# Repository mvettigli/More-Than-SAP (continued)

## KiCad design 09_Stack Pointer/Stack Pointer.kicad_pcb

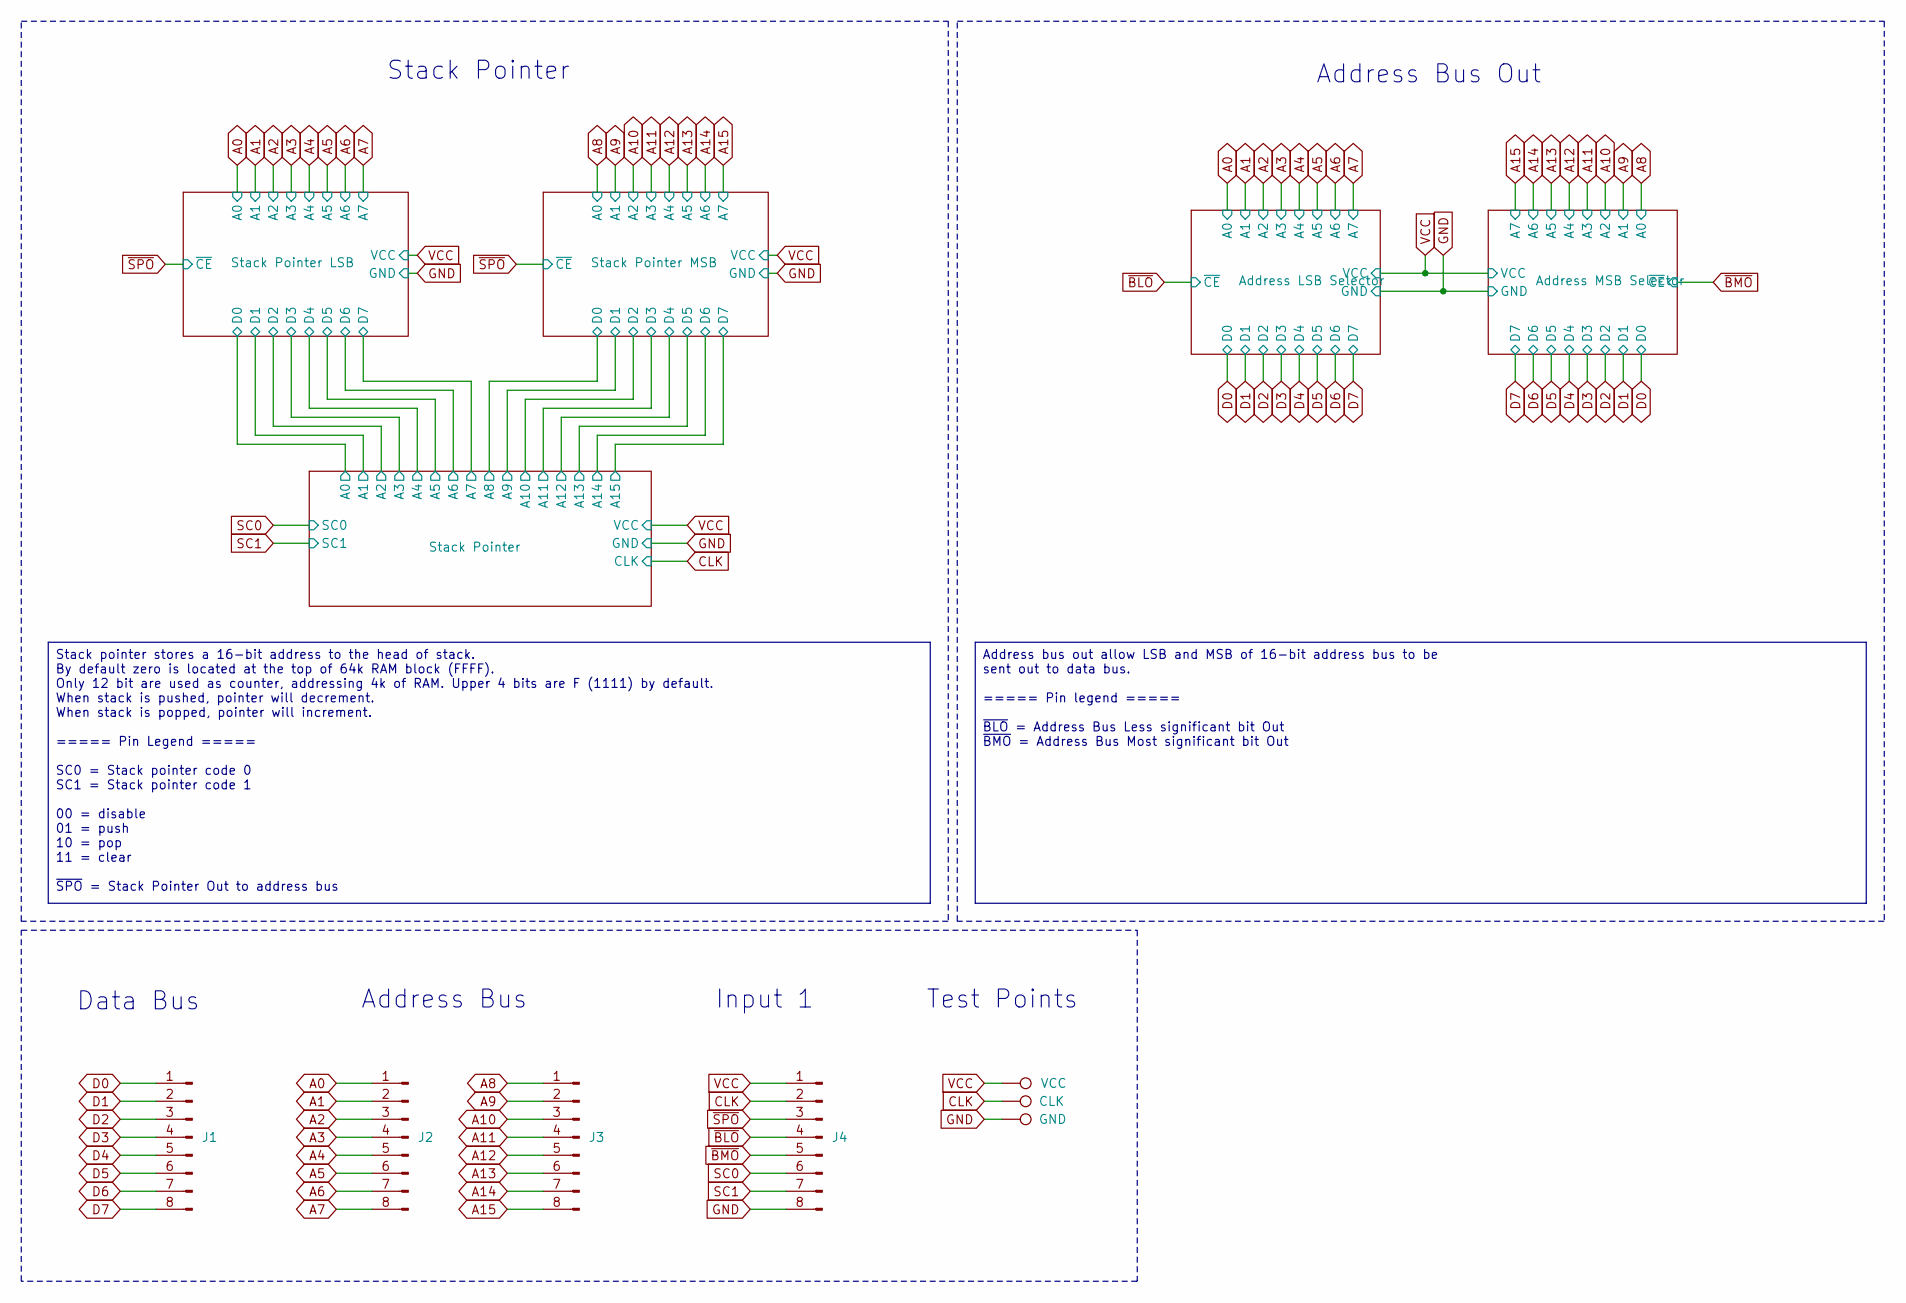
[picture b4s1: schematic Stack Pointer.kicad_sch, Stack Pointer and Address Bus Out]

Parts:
J1: Data bus; PinHeader_1x08_P2.54mm_Horizontal
J2: Address bus 1; PinHeader_1x08_P2.54mm_Horizontal
J3: Address bus 2; PinHeader_1x08_P2.54mm_Horizontal
J4: Input 1; PinHeader_1x08_P2.54mm_Horizontal
TP1: VCC; TestPoint_Loop_D3.50mm_Drill0.9mm_Beaded
TP2: CLK; TestPoint_Loop_D3.50mm_Drill0.9mm_Beaded
TP3: GND; TestPoint_Loop_D3.50mm_Drill0.9mm_Beaded

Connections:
A0: J2.1; also elsewhere on the board
A1: J2.2; also elsewhere on the board
A2: J2.3; also elsewhere on the board
A3: J2.4; also elsewhere on the board
A4: J2.5; also elsewhere on the board
A5: J2.6; also elsewhere on the board
A6: J2.7; also elsewhere on the board
A7: J2.8; also elsewhere on the board
A8: J3.1; also elsewhere on the board
A9: J3.2; also elsewhere on the board
A10: J3.3; also elsewhere on the board
A11: J3.4; also elsewhere on the board
A12: J3.5; also elsewhere on the board
A13: J3.6; also elsewhere on the board
A14: J3.7; also elsewhere on the board
A15: J3.8; also elsewhere on the board
CLK: J4.2, TP2.1; also elsewhere on the board
D0: J1.1; also elsewhere on the board
D1: J1.2; also elsewhere on the board
D2: J1.3; also elsewhere on the board
D3: J1.4; also elsewhere on the board
D4: J1.5; also elsewhere on the board
D5: J1.6; also elsewhere on the board
D6: J1.7; also elsewhere on the board
D7: J1.8; also elsewhere on the board
GND: J4.8, TP3.1; also elsewhere on the board
SC0: J4.6; also elsewhere on the board
SC1: J4.7; also elsewhere on the board
VCC: J4.1, TP1.1; also elsewhere on the board
~BLO: J4.4; also elsewhere on the board
~BMO: J4.5; also elsewhere on the board
~SPO: J4.3; also elsewhere on the board

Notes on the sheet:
Stack Pointer
Address Bus Out
Address Bus
Data Bus
Test Points
Input 1
Address bus out allow LSB and MSB of 16-bit address bus to be sent out to data bus. ===== Pin legend ===== ~{BLO} = Address Bus Less significant bit Out ~{BMO} = Address Bus Most significant bit Out
Stack pointer stores a 16-bit address to the head of stack. By default zero is located at the top of 64k RAM block (FFFF). Only 12 bit are used as counter, addressing 4k of RAM. Upper 4 bits are F (1111) by default. When stack is pushed, pointer will decrement. When stack is popped, pointer will in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

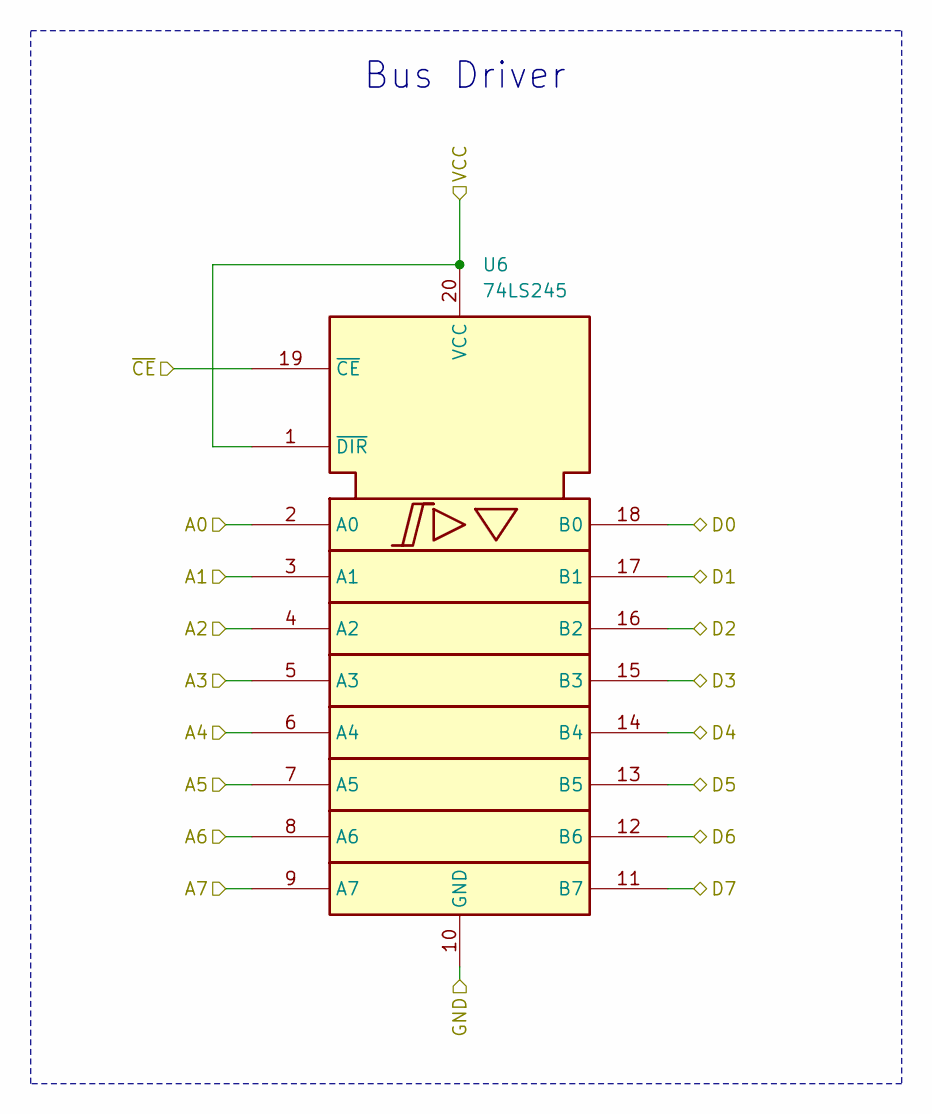
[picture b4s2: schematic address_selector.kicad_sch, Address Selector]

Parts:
U6: 74LS245; DIP-20_W7.62mm

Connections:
/Stack Pointer/A0: U6.18 (B0); also elsewhere on the board
/Stack Pointer/A1: U6.17 (B1); also elsewhere on the board
/Stack Pointer/A2: U6.16 (B2); also elsewhere on the board
/Stack Pointer/A3: U6.15 (B3); also elsewhere on the board
/Stack Pointer/A4: U6.14 (B4); also elsewhere on the board
/Stack Pointer/A5: U6.13 (B5); also elsewhere on the board
/Stack Pointer/A6: U6.12 (B6); also elsewhere on the board
/Stack Pointer/A7: U6.11 (B7); also elsewhere on the board
A0: U6.2 (A0); also elsewhere on the board
A1: U6.3 (A1); also elsewhere on the board
A2: U6.4 (A2); also elsewhere on the board
A3: U6.5 (A3); also elsewhere on the board
A4: U6.6 (A4); also elsewhere on the board
A5: U6.7 (A5); also elsewhere on the board
A6: U6.8 (A6); also elsewhere on the board
A7: U6.9 (A7); also elsewhere on the board
GND: U6.10 (GND); also elsewhere on the board
VCC: U6.1 (~DIR), U6.20 (VCC); also elsewhere on the board
~SPO: U6.19 (~CE); also elsewhere on the board

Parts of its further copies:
U7, U8, U9: 74LS245; DIP-20_W7.62mm

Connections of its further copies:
/Stack Pointer MSB/D0: U7.18 (B0); also elsewhere on the board
/Stack Pointer MSB/D1: U7.17 (B1); also elsewhere on the board
/Stack Pointer MSB/D2: U7.16 (B2); also elsewhere on the board
/Stack Pointer MSB/D3: U7.15 (B3); also elsewhere on the board
A0: U8.2 (A0); also elsewhere on the board
A1: U8.3 (A1); also elsewhere on the board
A2: U8.4 (A2); also elsewhere on the board
A3: U8.5 (A3); also elsewhere on the board
A4: U8.6 (A4); also elsewhere on the board
A5: U8.7 (A5); also elsewhere on the board
A6: U8.8 (A6); also elsewhere on the board
A7: U8.9 (A7); also elsewhere on the board
A8: U7.2 (A0), U9.2 (A0); also elsewhere on the board
A9: U7.3 (A1), U9.3 (A1); also elsewhere on the board
A10: U7.4 (A2), U9.4 (A2); also elsewhere on the board
A11: U7.5 (A3), U9.5 (A3); also elsewhere on the board
A12: U7.6 (A4), U9.6 (A4); also elsewhere on the board
A13: U7.7 (A5), U9.7 (A5); also elsewhere on the board
A14: U7.8 (A6), U9.8 (A6); also elsewhere on the board
A15: U7.9 (A7), U9.9 (A7); also elsewhere on the board
D0: U8.18 (B0), U9.18 (B0); also elsewhere on the board
D1: U8.17 (B1), U9.17 (B1); also elsewhere on the board
D2: U8.16 (B2), U9.16 (B2); also elsewhere on the board
D3: U8.15 (B3), U9.15 (B3); also elsewhere on the board
D4: U8.14 (B4), U9.14 (B4); also elsewhere on the board
D5: U8.13 (B5), U9.13 (B5); also elsewhere on the board
D6: U8.12 (B6), U9.12 (B6); also elsewhere on the board
D7: U8.11 (B7), U9.11 (B7); also elsewhere on the board
GND: U7.10 (GND), U8.10 (GND), U9.10 (GND); also elsewhere on the board
VCC: U7.1 (~DIR), U7.11 (B7), U7.12 (B6), U7.13 (B5), U7.14 (B4), U7.20 (VCC), U8.1 (~DIR), U8.20 (VCC), U9.1 (~DIR), U9.20 (VCC); also elsewhere on the board
~BLO: U8.19 (~CE); also elsewhere on the board
~BMO: U9.19 (~CE); also elsewhere on the board
~SPO: U7.19 (~CE); also elsewhere on the board

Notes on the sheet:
Bus Driver

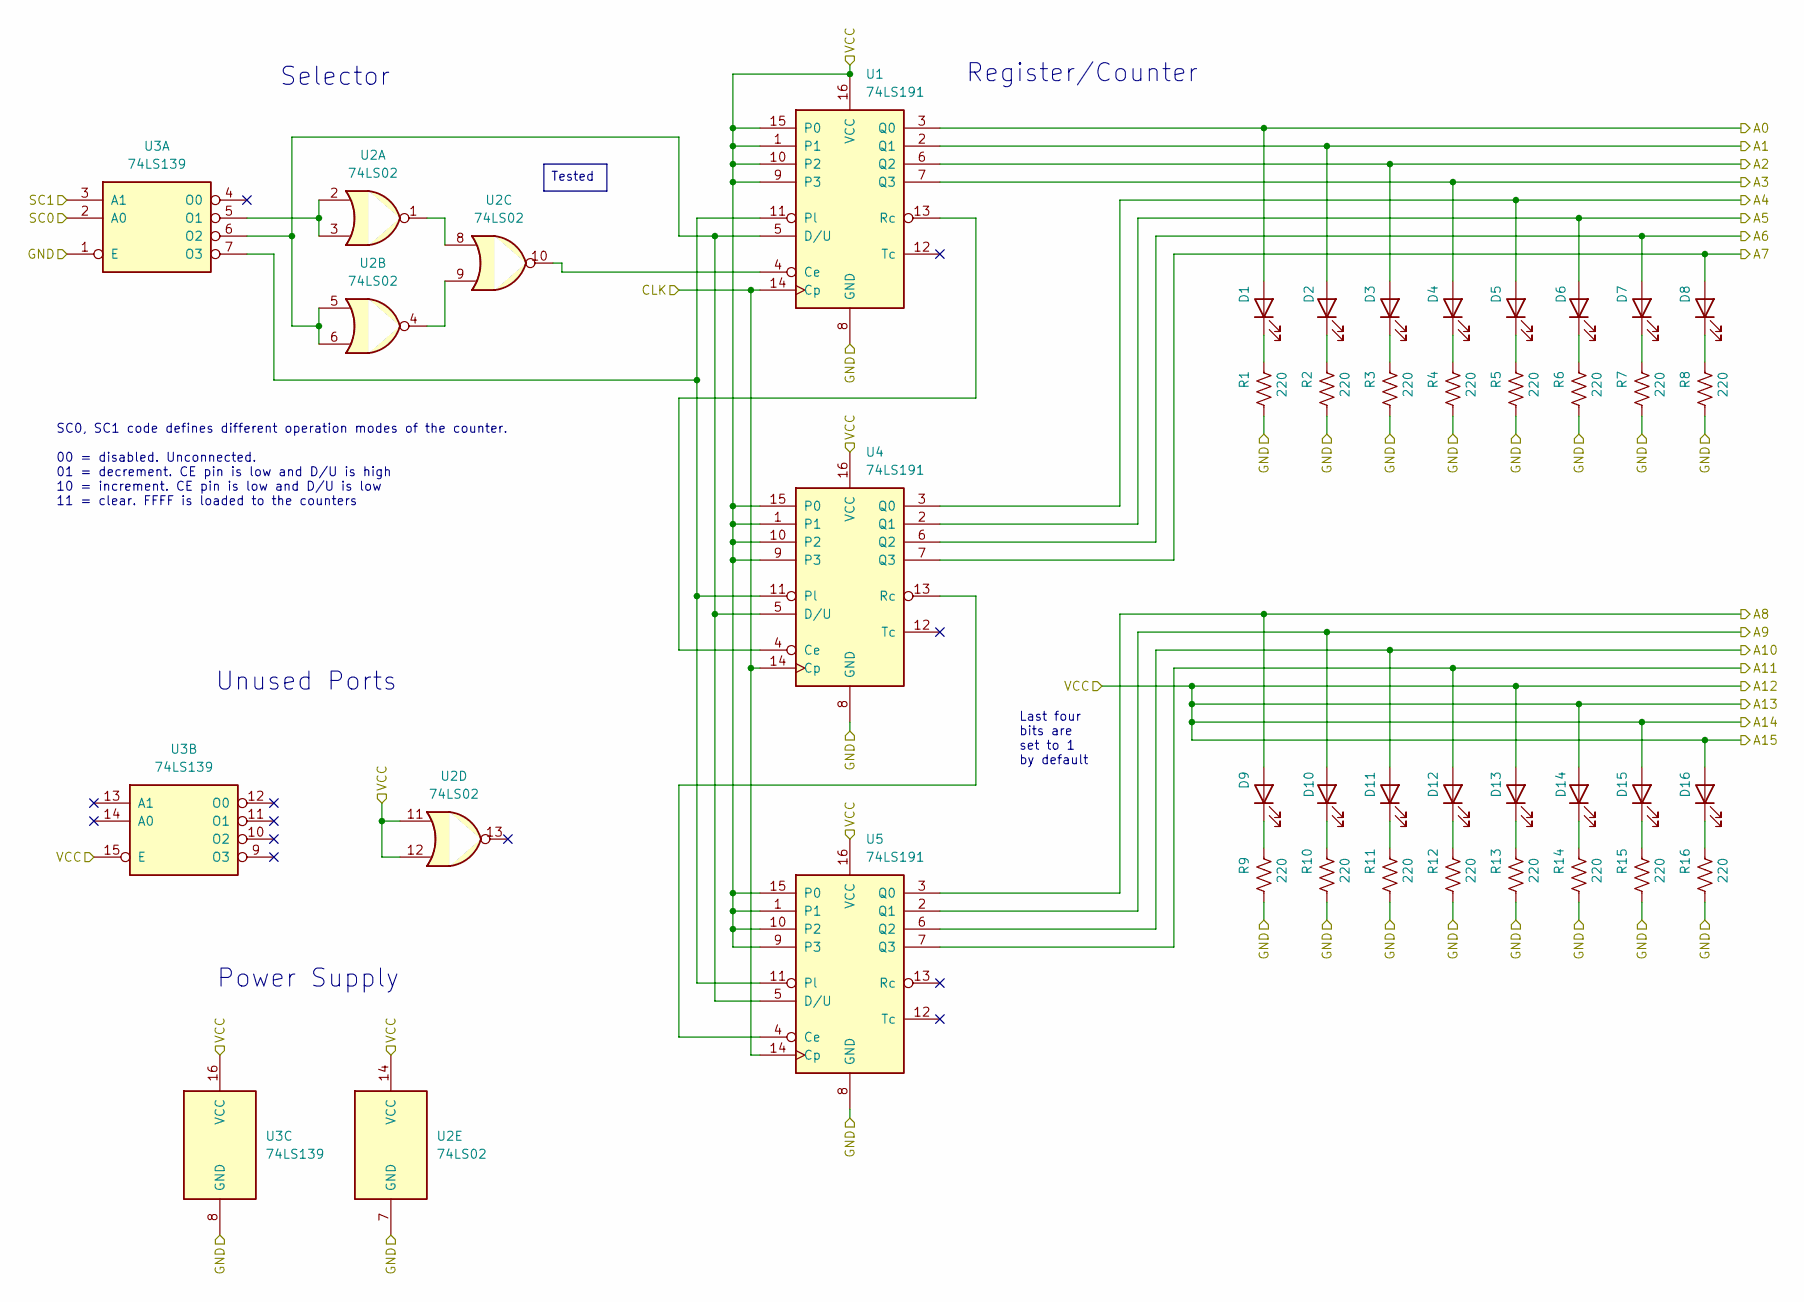
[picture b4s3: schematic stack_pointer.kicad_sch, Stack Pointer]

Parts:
D1, D2, D3, D4, D5, D6, D7, D8, D9, D10, D11, D12, D13, D14, D15, D16: GREEN; LED_D3.0mm
R1, R2, R3, R4, R5, R6, R7, R8, R9, R10, R11, R12, R13, R14, R15, R16: 220; R_Axial_DIN0207_L6.3mm_D2.5mm_P10.16mm_Horizontal
U1, U4, U5: 74LS191; DIP-16_W7.62mm
U2: 74LS02; DIP-14_W7.62mm
U3: 74LS139; DIP-16_W7.62mm

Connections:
/Stack Pointer MSB/D0: D9.2 (A), U5.3 (Q0); also elsewhere on the board
/Stack Pointer MSB/D1: D10.2 (A), U5.2 (Q1); also elsewhere on the board
/Stack Pointer MSB/D2: D11.2 (A), U5.6 (Q2); also elsewhere on the board
/Stack Pointer MSB/D3: D12.2 (A), U5.7 (Q3); also elsewhere on the board
/Stack Pointer/A0: D1.2 (A), U1.3 (Q0); also elsewhere on the board
/Stack Pointer/A1: D2.2 (A), U1.2 (Q1); also elsewhere on the board
/Stack Pointer/A2: D3.2 (A), U1.6 (Q2); also elsewhere on the board
/Stack Pointer/A3: D4.2 (A), U1.7 (Q3); also elsewhere on the board
/Stack Pointer/A4: D5.2 (A), U4.3 (Q0); also elsewhere on the board
/Stack Pointer/A5: D6.2 (A), U4.2 (Q1); also elsewhere on the board
/Stack Pointer/A6: D7.2 (A), U4.6 (Q2); also elsewhere on the board
/Stack Pointer/A7: D8.2 (A), U4.7 (Q3); also elsewhere on the board
CLK: U1.14 (Cp), U4.14 (Cp), U5.14 (Cp); also elsewhere on the board
GND: R1.2, R2.2, R3.2, R4.2, R5.2, R6.2, R7.2, R8.2, R9.2, R10.2, R11.2, R12.2, R13.2, R14.2, R15.2, R16.2, U1.8 (GND), U2.7 (GND), U3.1 (E), U3.8 (GND), U4.8 (GND), U5.8 (GND); also elsewhere on the board
unnamed: D1.1 (K), R1.1
unnamed: D2.1 (K), R2.1
unnamed: D3.1 (K), R3.1
unnamed: D4.1 (K), R4.1
unnamed: D5.1 (K), R5.1
unnamed: D6.1 (K), R6.1
unnamed: D7.1 (K), R7.1
unnamed: D8.1 (K), R8.1
unnamed: D9.1 (K), R9.1
unnamed: D10.1 (K), R10.1
unnamed: D11.1 (K), R11.1
unnamed: D12.1 (K), R12.1
unnamed: D13.1 (K), R13.1
unnamed: D14.1 (K), R14.1
unnamed: D15.1 (K), R15.1
unnamed: D16.1 (K), R16.1
unnamed: U1.4 (Ce), U2.10
unnamed: U1.5 (D/U), U2.5, U2.6, U3.6 (O2), U4.5 (D/U), U5.5 (D/U)
unnamed: U1.11 (Pl), U3.7 (O3), U4.11 (Pl), U5.11 (Pl)
unnamed: U1.13 (Rc), U4.4 (Ce)
unnamed: U2.1, U2.8
unnamed: U2.4, U2.9
unnamed: U2.2, U2.3, U3.5 (O1)
unnamed: U4.13 (Rc), U5.4 (Ce)
SC0: U3.2 (A0); also elsewhere on the board
SC1: U3.3 (A1); also elsewhere on the board
VCC: D13.2 (A), D14.2 (A), D15.2 (A), D16.2 (A), U1.1, U1.9 (P3), U1.10 (P2), U1.15 (P0), U1.16 (VCC), U2.11, U2.12, U2.14 (VCC), U3.15 (E), U3.16 (VCC), U4.1, U4.9 (P3), U4.10 (P2), U4.15 (P0), U4.16 (VCC), U5.1, U5.9 (P3), U5.10 (P2), U5.15 (P0), U5.16 (VCC); also elsewhere on the board

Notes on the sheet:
Selector
Unused Ports
Power Supply
Register/Counter
SC0, SC1 code defines different operation modes of the counter. 00 = disabled. Unconnected. 01 = decrement. CE pin is low and D/U is high 10 = increment. CE pin is low and D/U is low 11 = clear. FFFF is loaded to the counters
Last four bits are set to 1 by default
Tested

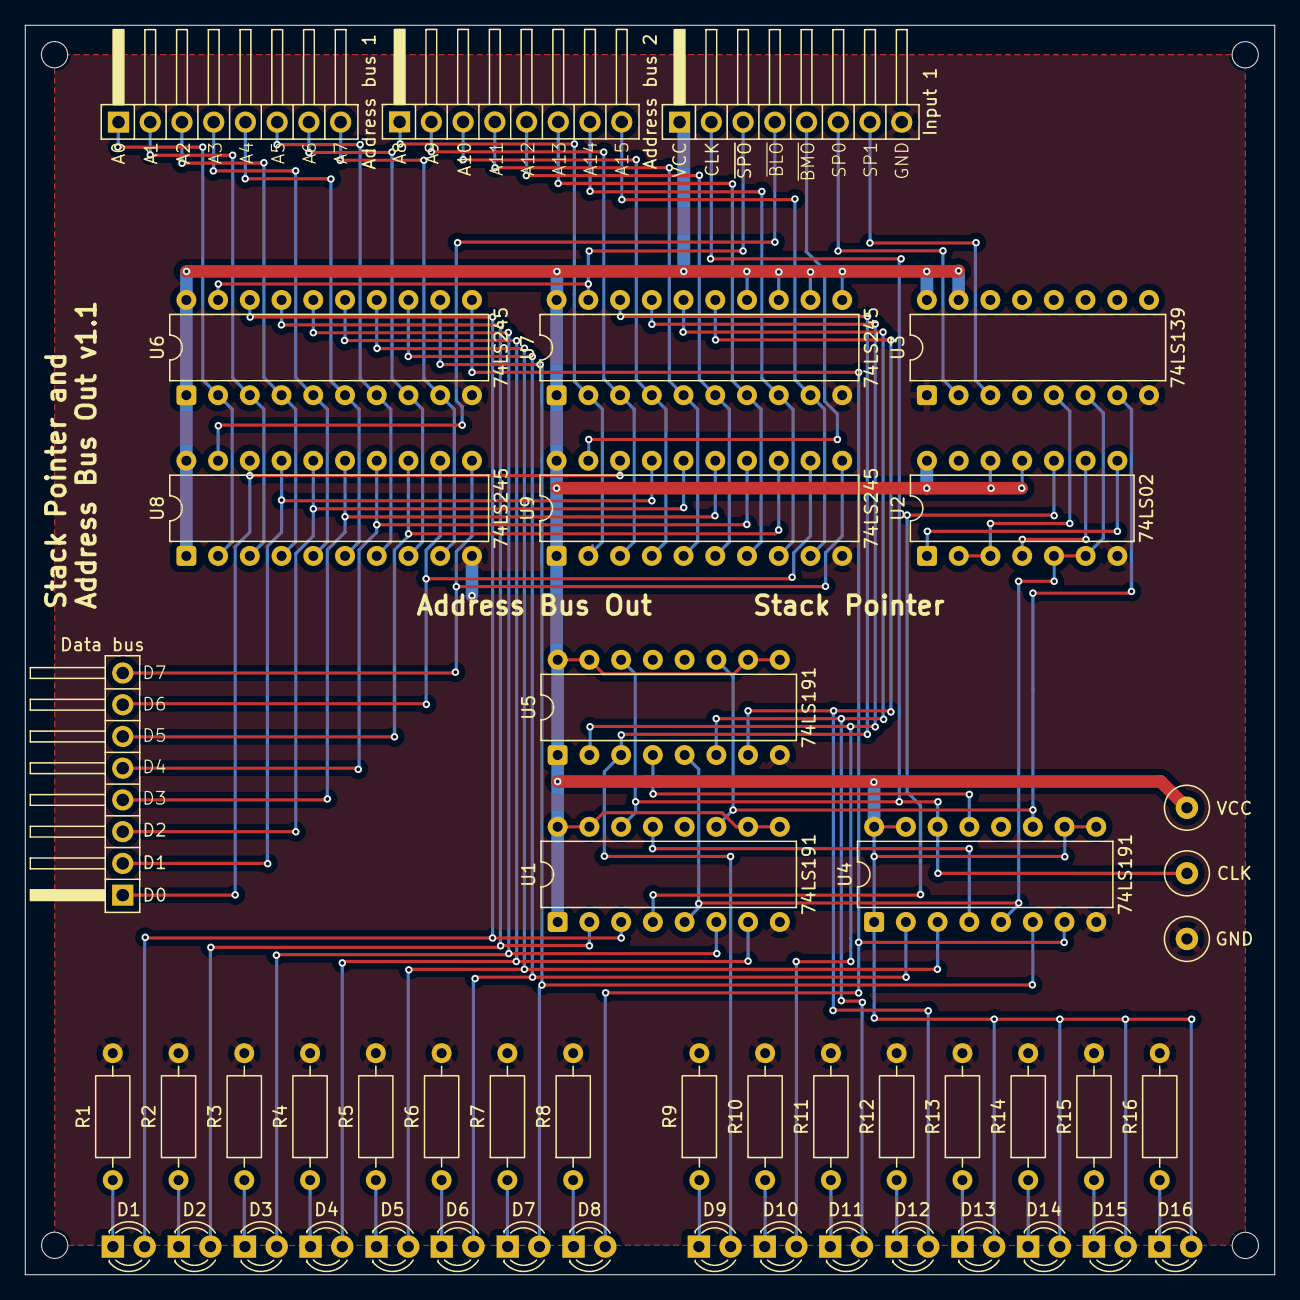
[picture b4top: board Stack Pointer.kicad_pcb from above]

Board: 2 copper layers, 100.0 x 100.0 mm, 48 parts (0 on the bottom side), 68 nets.

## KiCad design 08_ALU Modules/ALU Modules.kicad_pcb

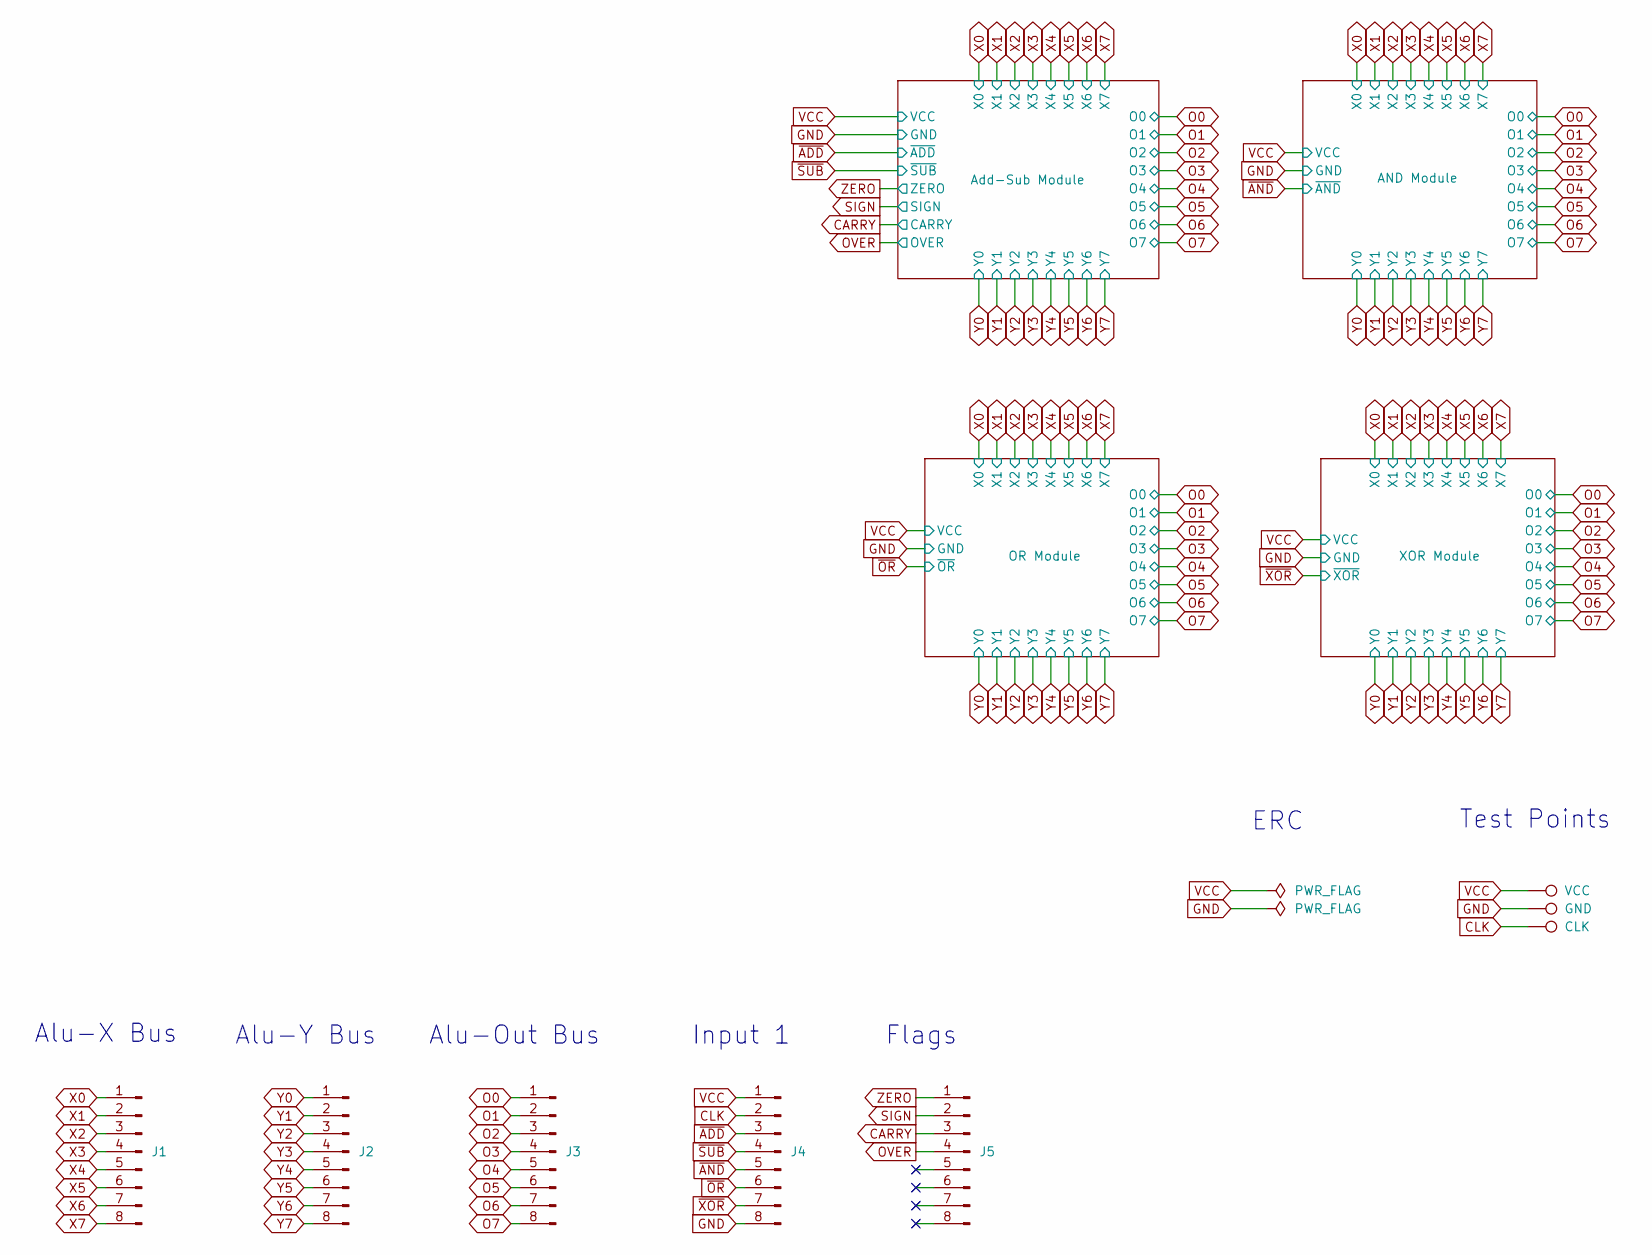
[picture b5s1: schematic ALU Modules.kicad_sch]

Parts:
J1: Alu-X Bus; PinHeader_1x08_P2.54mm_Horizontal
J2: Alu-Y Bus; PinHeader_1x08_P2.54mm_Horizontal
J3: Alu-Out Bus; PinHeader_1x08_P2.54mm_Horizontal
J4: Input 1; PinHeader_1x08_P2.54mm_Horizontal
J5: Flags; PinHeader_1x08_P2.54mm_Horizontal
TP1: VCC; TestPoint_Loop_D3.50mm_Drill0.9mm_Beaded
TP2: GND; TestPoint_Loop_D3.50mm_Drill0.9mm_Beaded
TP3: CLK; TestPoint_Loop_D3.50mm_Drill0.9mm_Beaded

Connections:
CARRY: J5.3; also elsewhere on the board
CLK: J4.2, TP3.1
GND: J4.8, TP2.1; also elsewhere on the board
O0: J3.1; also elsewhere on the board
O1: J3.2; also elsewhere on the board
O2: J3.3; also elsewhere on the board
O3: J3.4; also elsewhere on the board
O4: J3.5; also elsewhere on the board
O5: J3.6; also elsewhere on the board
O6: J3.7; also elsewhere on the board
O7: J3.8; also elsewhere on the board
OVER: J5.4; also elsewhere on the board
SIGN: J5.2; also elsewhere on the board
VCC: J4.1, TP1.1; also elsewhere on the board
X0: J1.1; also elsewhere on the board
X1: J1.2; also elsewhere on the board
X2: J1.3; also elsewhere on the board
X3: J1.4; also elsewhere on the board
X4: J1.5; also elsewhere on the board
X5: J1.6; also elsewhere on the board
X6: J1.7; also elsewhere on the board
X7: J1.8; also elsewhere on the board
Y0: J2.1; also elsewhere on the board
Y1: J2.2; also elsewhere on the board
Y2: J2.3; also elsewhere on the board
Y3: J2.4; also elsewhere on the board
Y4: J2.5; also elsewhere on the board
Y5: J2.6; also elsewhere on the board
Y6: J2.7; also elsewhere on the board
Y7: J2.8; also elsewhere on the board
ZERO: J5.1; also elsewhere on the board
~ADD: J4.3; also elsewhere on the board
~AND: J4.5; also elsewhere on the board
~OR: J4.6; also elsewhere on the board
~SUB: J4.4; also elsewhere on the board
~XOR: J4.7; also elsewhere on the board

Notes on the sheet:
Test Points
Flags
Alu-X Bus
Alu-Y Bus
Alu-Out Bus
Input 1
ERC

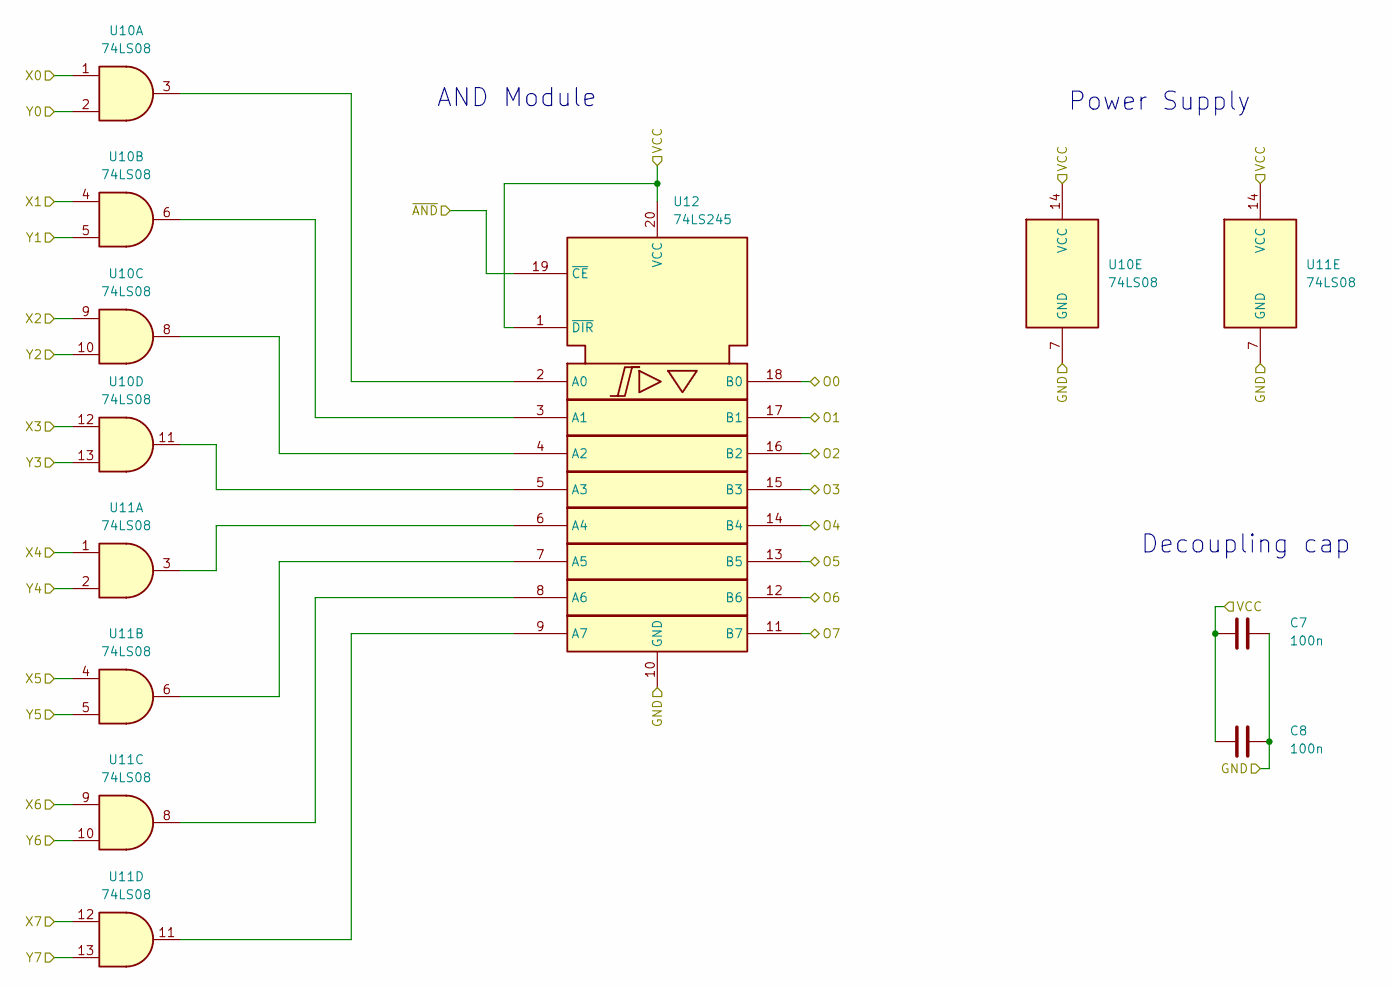
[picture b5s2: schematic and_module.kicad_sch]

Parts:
C7, C8: 100n; C_Disc_D3.0mm_W1.6mm_P2.50mm
U10, U11: 74LS08; DIP-14_W7.62mm
U12: 74LS245; DIP-20_W7.62mm

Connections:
GND: C7.2, C8.2, U10.7 (GND), U11.7 (GND), U12.10 (GND); also elsewhere on the board
unnamed: U10.3, U12.2 (A0)
unnamed: U10.6, U12.3 (A1)
unnamed: U10.8, U12.4 (A2)
unnamed: U10.11, U12.5 (A3)
unnamed: U11.3, U12.6 (A4)
unnamed: U11.6, U12.7 (A5)
unnamed: U11.8, U12.8 (A6)
unnamed: U11.11, U12.9 (A7)
O0: U12.18 (B0); also elsewhere on the board
O1: U12.17 (B1); also elsewhere on the board
O2: U12.16 (B2); also elsewhere on the board
O3: U12.15 (B3); also elsewhere on the board
O4: U12.14 (B4); also elsewhere on the board
O5: U12.13 (B5); also elsewhere on the board
O6: U12.12 (B6); also elsewhere on the board
O7: U12.11 (B7); also elsewhere on the board
VCC: C7.1, C8.1, U10.14 (VCC), U11.14 (VCC), U12.1 (~DIR), U12.20 (VCC); also elsewhere on the board
X0: U10.1; also elsewhere on the board
X1: U10.4; also elsewhere on the board
X2: U10.9; also elsewhere on the board
X3: U10.12; also elsewhere on the board
X4: U11.1; also elsewhere on the board
X5: U11.4; also elsewhere on the board
X6: U11.9; also elsewhere on the board
X7: U11.12; also elsewhere on the board
Y0: U10.2; also elsewhere on the board
Y1: U10.5; also elsewhere on the board
Y2: U10.10; also elsewhere on the board
Y3: U10.13; also elsewhere on the board
Y4: U11.2; also elsewhere on the board
Y5: U11.5; also elsewhere on the board
Y6: U11.10; also elsewhere on the board
Y7: U11.13; also elsewhere on the board
~AND: U12.19 (~CE); also elsewhere on the board

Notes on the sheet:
AND Module
Power Supply
Decoupling cap

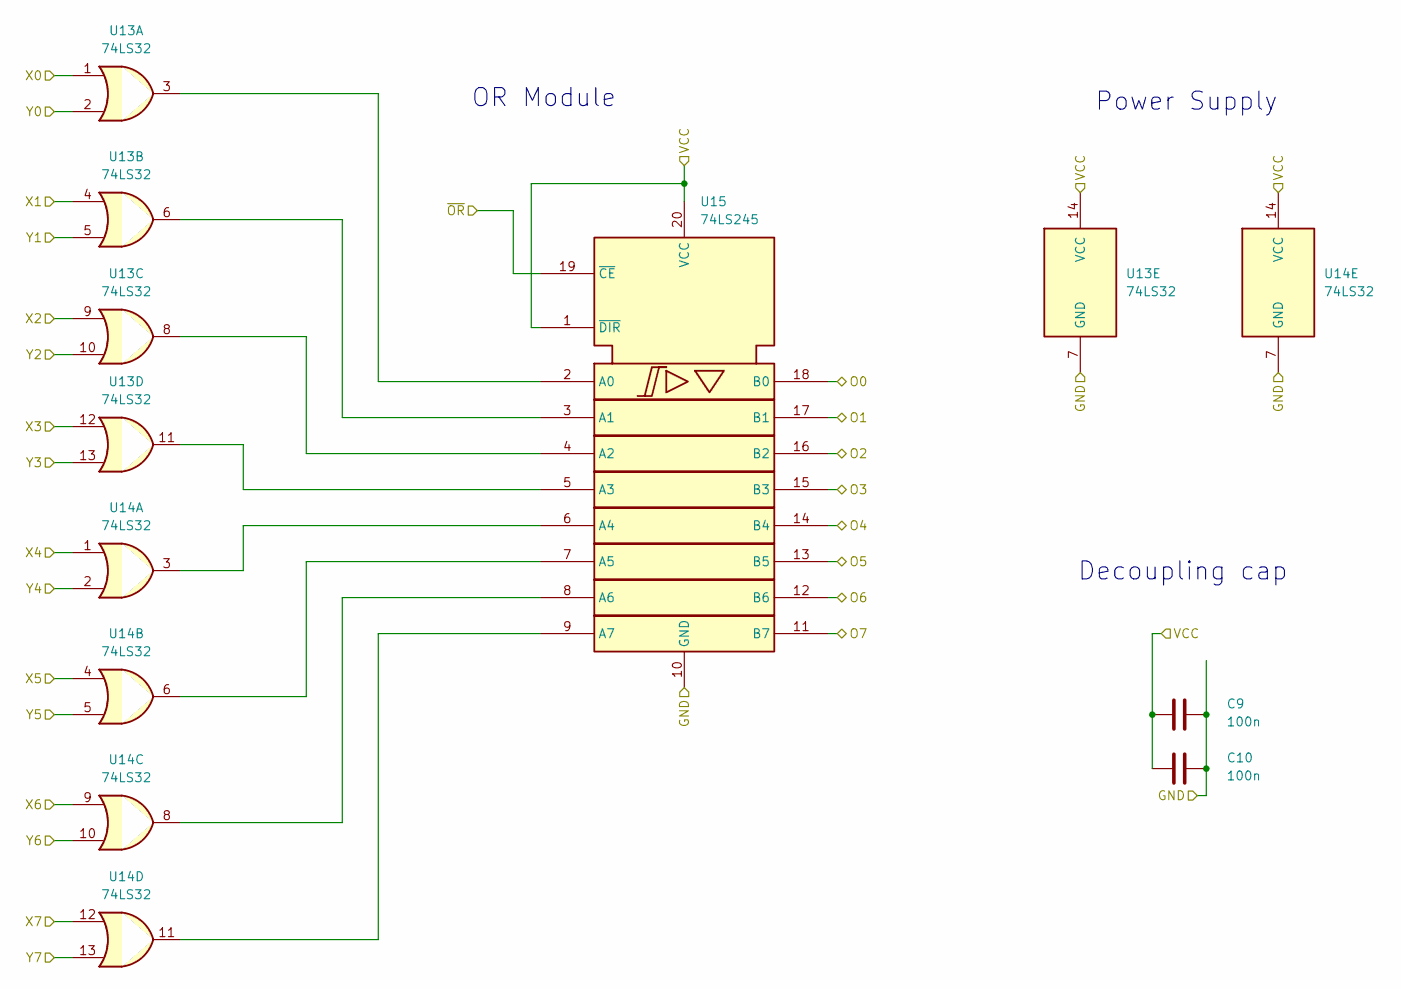
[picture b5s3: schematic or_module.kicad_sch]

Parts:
C9, C10: 100n; C_Disc_D3.0mm_W1.6mm_P2.50mm
U13, U14: 74LS32; DIP-14_W7.62mm
U15: 74LS245; DIP-20_W7.62mm

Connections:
GND: C9.2, C10.2, U13.7 (GND), U14.7 (GND), U15.10 (GND); also elsewhere on the board
unnamed: U13.3, U15.2 (A0)
unnamed: U13.6, U15.3 (A1)
unnamed: U13.8, U15.4 (A2)
unnamed: U13.11, U15.5 (A3)
unnamed: U14.3, U15.6 (A4)
unnamed: U14.6, U15.7 (A5)
unnamed: U14.8, U15.8 (A6)
unnamed: U14.11, U15.9 (A7)
O0: U15.18 (B0); also elsewhere on the board
O1: U15.17 (B1); also elsewhere on the board
O2: U15.16 (B2); also elsewhere on the board
O3: U15.15 (B3); also elsewhere on the board
O4: U15.14 (B4); also elsewhere on the board
O5: U15.13 (B5); also elsewhere on the board
O6: U15.12 (B6); also elsewhere on the board
O7: U15.11 (B7); also elsewhere on the board
VCC: C9.1, C10.1, U13.14 (VCC), U14.14 (VCC), U15.1 (~DIR), U15.20 (VCC); also elsewhere on the board
X0: U13.1; also elsewhere on the board
X1: U13.4; also elsewhere on the board
X2: U13.9; also elsewhere on the board
X3: U13.12; also elsewhere on the board
X4: U14.1; also elsewhere on the board
X5: U14.4; also elsewhere on the board
X6: U14.9; also elsewhere on the board
X7: U14.12; also elsewhere on the board
Y0: U13.2; also elsewhere on the board
Y1: U13.5; also elsewhere on the board
Y2: U13.10; also elsewhere on the board
Y3: U13.13; also elsewhere on the board
Y4: U14.2; also elsewhere on the board
Y5: U14.5; also elsewhere on the board
Y6: U14.10; also elsewhere on the board
Y7: U14.13; also elsewhere on the board
~OR: U15.19 (~CE); also elsewhere on the board

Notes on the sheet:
Decoupling cap
Power Supply
OR Module
